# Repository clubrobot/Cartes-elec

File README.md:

View this project on [CADLAB.io](https://cadlab.io/project/28321). 

# Cartes-elec
Repo de toutes les cartes électroniques utilisées par le CRINSA. Commencé en 2025 sous Kicad 8.0

TODO:
 - Finir le pcb principal
 - Finir le pcb règle
 - Faire le PCB du lidar
 - Faire le PCB du controlleur des afficheurs Leds-Matrix (ou en tout cas le reprogrammer)
 - Faire les 3 PCBs des Superstars

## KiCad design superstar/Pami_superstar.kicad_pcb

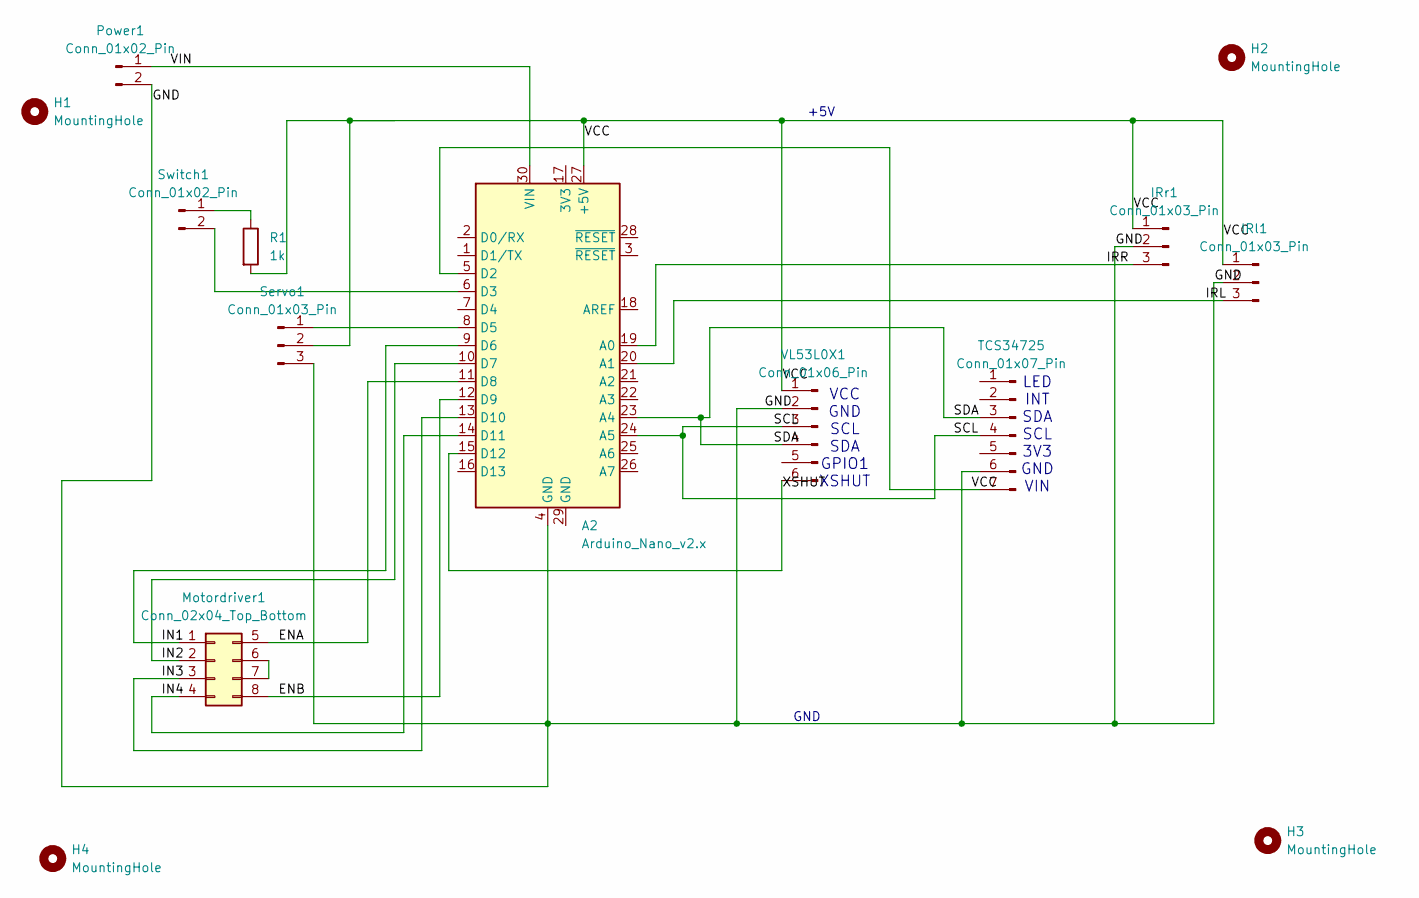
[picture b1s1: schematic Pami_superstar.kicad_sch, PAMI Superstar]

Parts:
A2: Arduino_Nano_v2.x; Arduino_Nano
H1, H2, H3, H4: MountingHole; MountingHole_3.2mm_M3
IRl1: Conn_01x03_Pin; JST_EH_B3B-EH-A_1x03_P2.50mm_Vertical
IRr1: Conn_01x03_Pin; JST_EH_B3B-EH-A_1x03_P2.50mm_Vertical
Motordriver1: Conn_02x04_Top_Bottom; JST_JWPF_B08B-JWPF-SK-R_2x04_P2.00mm_Vertical
Power1: Conn_01x02_Pin; JST_EH_B2B-EH-A_1x02_P2.50mm_Vertical
R1: 1k; R_Axial_DIN0204_L3.6mm_D1.6mm_P7.62mm_Horizontal
Servo1: Conn_01x03_Pin; JST_EH_B3B-EH-A_1x03_P2.50mm_Vertical
Switch1: Conn_01x02_Pin; JST_EH_B2B-EH-A_1x02_P2.50mm_Vertical
TCS34725: Conn_01x07_Pin; JST_EH_B7B-EH-A_1x07_P2.50mm_Vertical
VL53L0X1: Conn_01x06_Pin; JST_EH_B6B-EH-A_1x06_P2.50mm_Vertical

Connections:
/ENA: A2.11 (D8), Motordriver1.5
/ENB: A2.12 (D9), Motordriver1.8
/GND: A2.4 (GND), IRl1.2, IRr1.2, Power1.2, Servo1.3, TCS34725.6, VL53L0X1.2
/IN1: A2.9 (D6), Motordriver1.1
/IN2: A2.10 (D7), Motordriver1.2
/IN3: A2.13 (D10), Motordriver1.3
/IN4: A2.14 (D11), Motordriver1.4
/IRL: A2.20 (A1), IRl1.3
/IRR: A2.19 (A0), IRr1.3
/SCL: A2.24 (A5), TCS34725.4, VL53L0X1.3
/SDA: A2.23 (A4), TCS34725.3, VL53L0X1.4
/VCC: A2.5 (D2), A2.27 (+5V), IRl1.1, IRr1.1, R1.2, Servo1.2, TCS34725.7, VL53L0X1.1
/VIN: A2.30 (VIN), Power1.1
/XSHUT: A2.15 (D12), VL53L0X1.6
unnamed: A2.6 (D3), Switch1.2
unnamed: A2.8 (D5), Servo1.1
unnamed: Motordriver1.6, Motordriver1.7
unnamed: R1.1, Switch1.1

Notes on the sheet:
LED INT SDA SCL 3V3 GND VIN
VCC GND SCL SDA GPIO1 XSHUT
GND
+5V

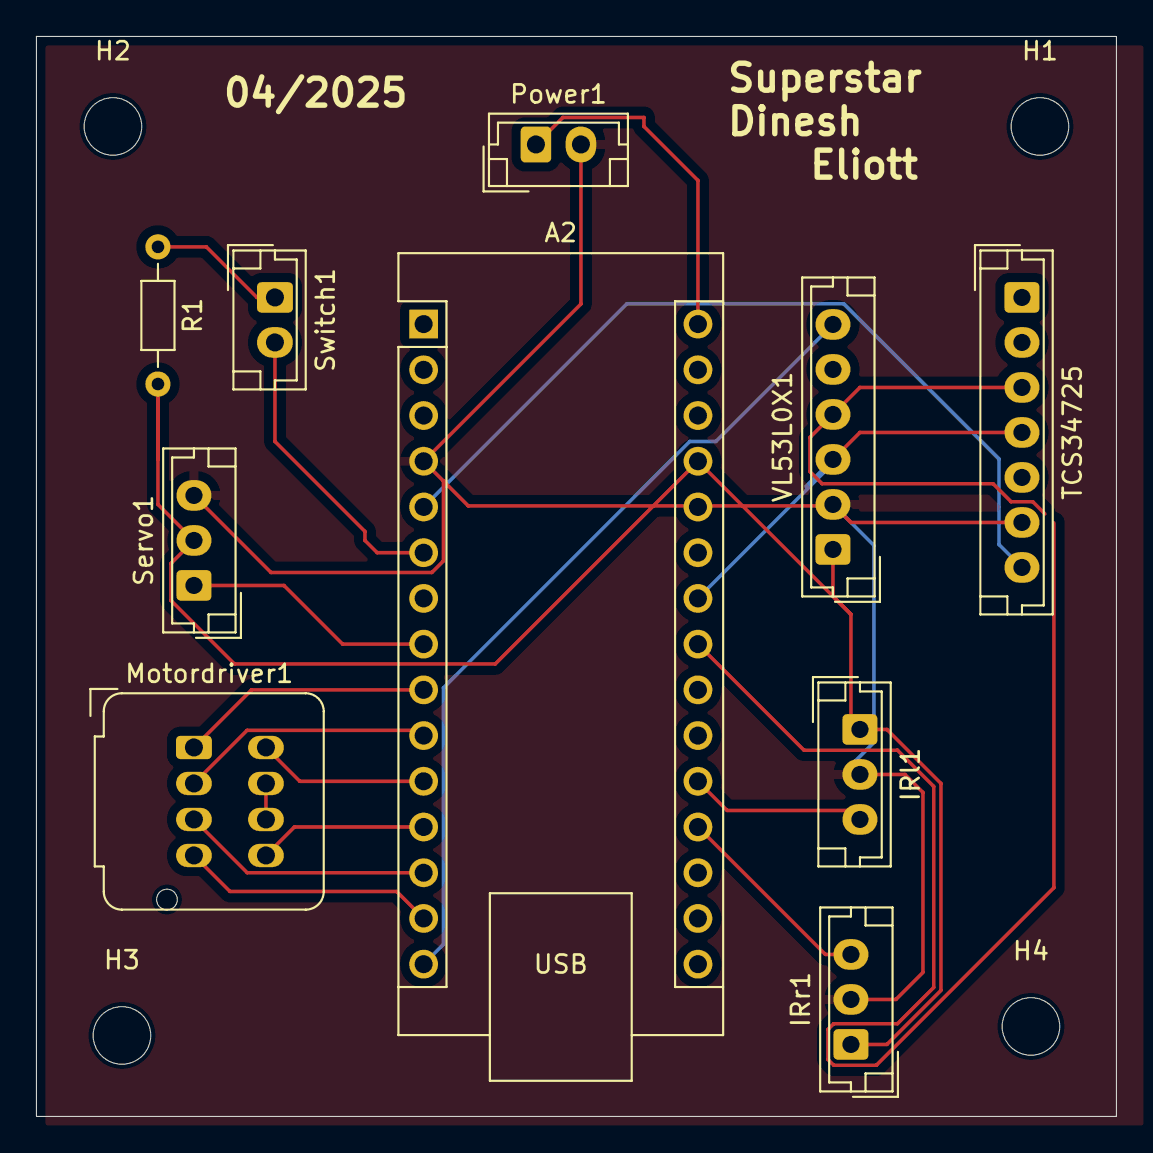
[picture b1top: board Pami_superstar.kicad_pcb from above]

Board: 2 copper layers, 60.0 x 60.0 mm, 14 parts (0 on the bottom side), 18 nets.

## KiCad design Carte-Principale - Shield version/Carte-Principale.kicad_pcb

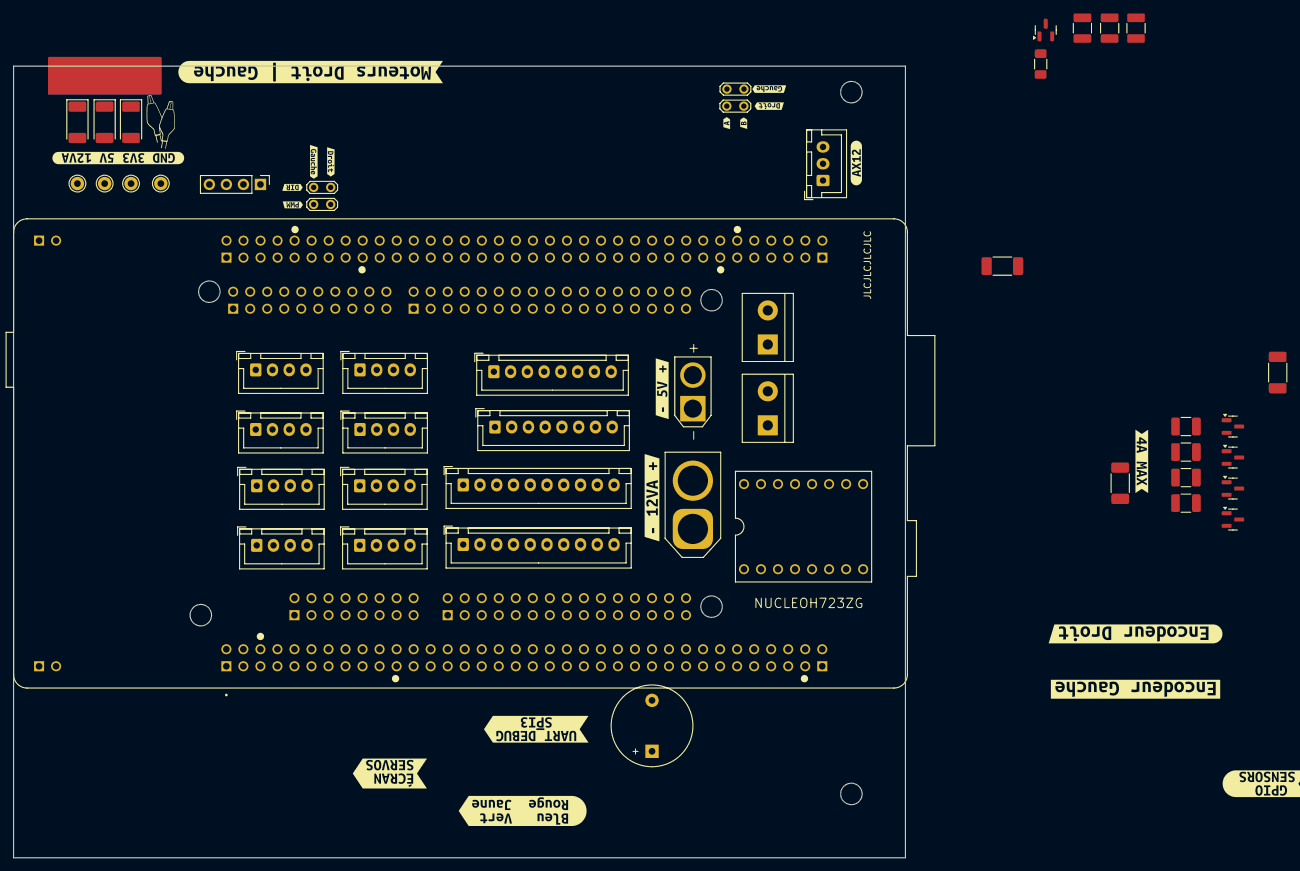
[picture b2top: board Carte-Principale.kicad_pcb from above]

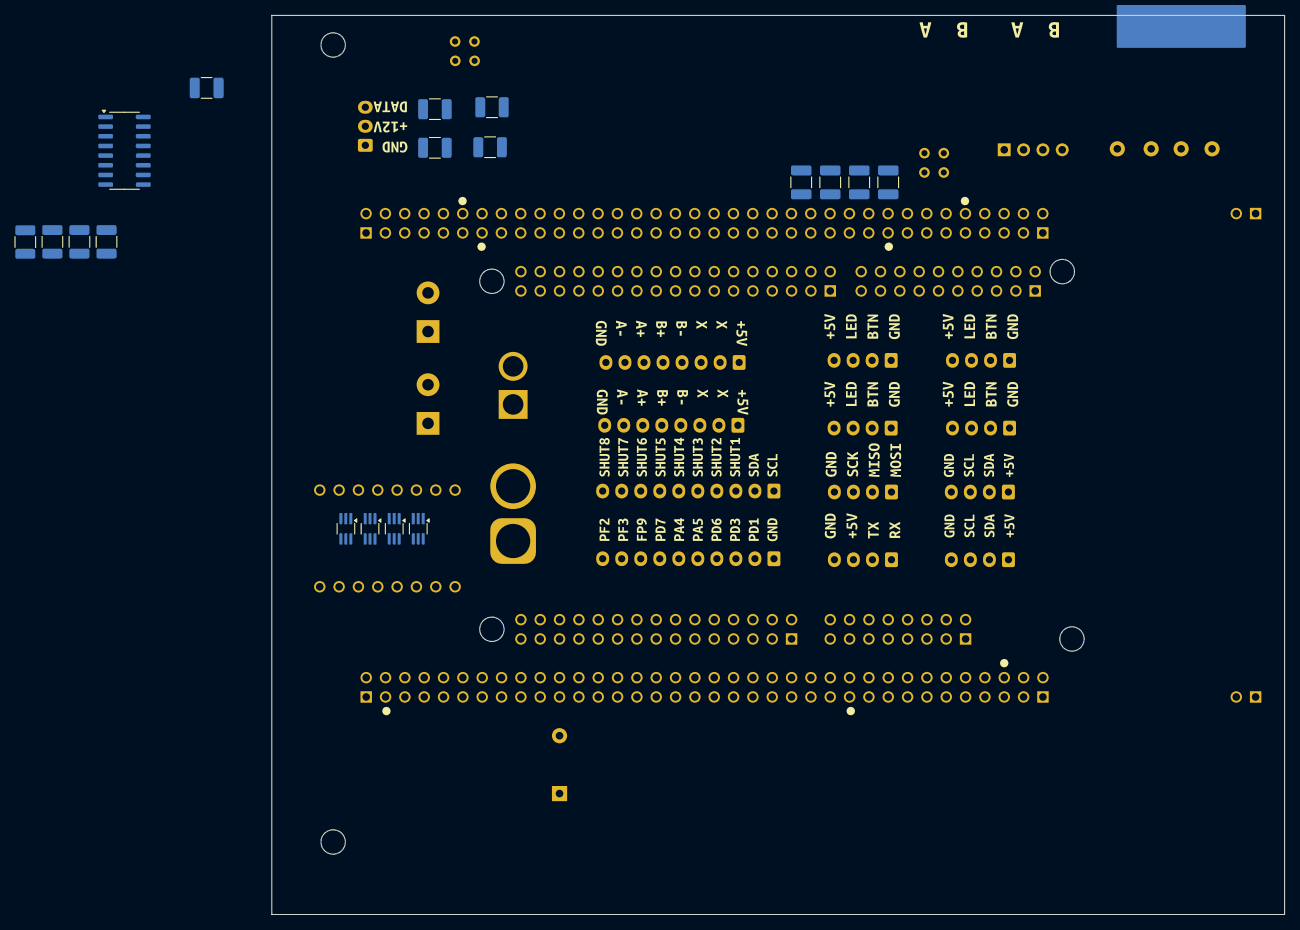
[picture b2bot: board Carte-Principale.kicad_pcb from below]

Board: 2 copper layers, 133.1 x 118.1 mm, 107 parts (34 on the bottom side), 80 nets, no tracks yet.

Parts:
BZ1: Buzzer; Buzzer_12x9.5RM7.6
C3, C4, C5, C6: 100n; C_1210_3225Metric_Pad1.33x2.70mm_HandSolder
C7: 0.1µ; C_1210_3225Metric_Pad1.33x2.70mm_HandSolder
D5: 5V; LED_2010_5025Metric_Pad1.52x2.65mm_HandSolder
D6: 3V3; LED_2010_5025Metric_Pad1.52x2.65mm_HandSolder
D7: 12VA; LED_2010_5025Metric_Pad1.52x2.65mm_HandSolder
DRV1: DRV8844_BREAKOUT_BOARD
F1, F2: 5A; Fuse_2010_5025Metric_Pad1.52x2.65mm_HandSolder
F3: 1.3A; Fuse_2010_5025Metric_Pad1.52x2.65mm_HandSolder
G1: LOGO
H1, H2, H3, H4: MountingHole; MountingHole_3.2mm_M3
J1: Moteur_Gauche; TerminalBlock_bornier-2_P5.08mm
J2: GND; PinHeader_1x04_P2.54mm_Vertical
J3: 12VA; AMASS_XT60-M_1x02_P7.20mm_Vertical
J4: 5V; AMASS_XT30U-M_1x02_P5.0mm_Vertical
J5: Moteur_Droit; TerminalBlock_bornier-2_P5.08mm
J6: UART_Debug; JST_XH_B4B-XH-A_1x04_P2.50mm_Vertical
J7: GPIO; JST_XH_B10B-XH-A_1x10_P2.50mm_Vertical
J8: Encodeur_D; JST_XH_B8B-XH-A_1x08_P2.50mm_Vertical
J9: SPI3; JST_XH_B4B-XH-A_1x04_P2.50mm_Vertical
J10: Sensors; JST_XH_B10B-XH-A_1x10_P2.50mm_Vertical
J13: Encodeur_G; JST_XH_B8B-XH-A_1x08_P2.50mm_Vertical
J15: AX12; JST_XH_B3B-XH-A_1x03_P2.50mm_Vertical
J18: PCA9685; JST_XH_B4B-XH-A_1x04_P2.50mm_Vertical
J21: I2C Screen; JST_XH_B4B-XH-A_1x04_P2.50mm_Vertical
Q1: BC817; SOT-23
Q2, Q3, Q4, Q5: BSS138; SOT-23
R1, R3, R4: R; R_1210_3225Metric_Pad1.30x2.65mm_HandSolder
R2: R; R_1206_3216Metric_Pad1.30x1.75mm_HandSolder
R9, R10, R11, R12: 10k; R_1210_3225Metric_Pad1.30x2.65mm_HandSolder
R27, R28, R29, R30: 100; R_1210_3225Metric_Pad1.30x2.65mm_HandSolder
R31, R32, R33, R34: 10K; R_1210_3225Metric_Pad1.30x2.65mm_HandSolder
SW1: Rouge; JST_XH_B4B-XH-A_1x04_P2.50mm_Vertical
SW2: Bleu; JST_XH_B4B-XH-A_1x04_P2.50mm_Vertical
SW3: Jaune; JST_XH_B4B-XH-A_1x04_P2.50mm_Vertical
SW4: Vert; JST_XH_B4B-XH-A_1x04_P2.50mm_Vertical
TP1: 3V3; Pin_D1.0mm_L10.0mm
TP2: GND; Pin_D1.0mm_L10.0mm
TP3: 5V; Pin_D1.0mm_L10.0mm
TP5: 12VA; Pin_D1.0mm_L10.0mm
TP6: Test_PWM; TestPoint_2Pads_Pitch2.54mm_Drill0.8mm
TP7: Test_DIR; TestPoint_2Pads_Pitch2.54mm_Drill0.8mm
TP8: Test_Gauche; TestPoint_2Pads_Pitch2.54mm_Drill0.8mm
TP9: Test_Droit; TestPoint_2Pads_Pitch2.54mm_Drill0.8mm
U2: NUCLEOH723ZG; MODULE_NUCLEOH723ZG
U3: AM26LV32xD; SOIC-16_3.9x9.9mm_P1.27mm
U4, U5, U6, U7: 74LVC1G3157; SOT-363_SC-70-6_Handsoldering
kibuzzard-2: G***; kibuzzard-66C478F6
kibuzzard-3: G***; kibuzzard-66C08D4F
kibuzzard-4: G***; kibuzzard-66C08D66
kibuzzard-5: G***; kibuzzard-66C08EFC
kibuzzard-7, kibuzzard-23: G***; kibuzzard-66C09269
kibuzzard-8, kibuzzard-19: G***; kibuzzard-66C0927B
kibuzzard-10: G***; kibuzzard-66C092E0
kibuzzard-22: G***; kibuzzard-66C09293
kibuzzard-24: G***; kibuzzard-66C0929D
kibuzzard-27: G***; kibuzzard-66C0922C
kibuzzard-28, kibuzzard-29: G***; kibuzzard-66C091DE
kibuzzard-30: G***; kibuzzard-66C09044
kibuzzard-34, kibuzzard-37: G***; kibuzzard-66C090AC
kibuzzard-35: G***; kibuzzard-66C09018
kibuzzard-38, kibuzzard-39, kibuzzard-40, kibuzzard-41: G***; kibuzzard-66C08FE4
kibuzzard-66F08110: G***; kibuzzard-66F08110
kibuzzard-66F08121: G***; kibuzzard-66F08121
kibuzzard-66FDA353: G***; kibuzzard-66FDA353
kibuzzard-67548A22: G***; kibuzzard-67548A22
kibuzzard-67548BCB: G***; kibuzzard-67548BCB
kibuzzard-675489B9: G***; kibuzzard-675489B9
kibuzzard-675489F8: G***; kibuzzard-675489F8
kibuzzard-675739BC: G***; kibuzzard-675739BC
kibuzzard-6754898D: G***; kibuzzard-6754898D
kibuzzard-6757392E: G***; kibuzzard-6757392E
kibuzzard-67547681: G***; kibuzzard-67547681
kibuzzard-67548783: G***; kibuzzard-67548783
kibuzzard-67548923: G***; kibuzzard-67548923
kibuzzard-67573990: G***; kibuzzard-67573990

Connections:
+3.3V: C3.2, C4.2, C5.2, C6.2, C7.1, F3.2, R1.1, TP1.1, U3.4 (G), U3.16 (VDD), U4.5 (VCC), U5.5 (VCC), U6.5 (VCC), U7.5 (VCC)
+5V: BZ1.1 (+), DRV1.SLP, F2.2, J6.3, J8.1, J13.1, J18.1, J21.1, R3.1, R31.2, R32.2, R33.2, R34.2, SW1.4 (A), SW2.4 (A), SW3.4 (A), SW4.4 (A), TP3.1, U2.CN11_6 (5V_EXT)
+12VA: DRV1.VMOT, F1.2, J15.2, R4.1, TP5.1
/AX12_RX: J15.3, U2.CN7_1 (D16/I2S_A_MCK), U2.CN7_11 (D21/I2S_B_MCK)
/DEBUG_RX: J6.1, U2.CN11_69 (PD9)
/DEBUG_TX: J6.2, U2.CN12_10 (PD8)
/Encodeur_Droit_A: TP9.1, U2.CN10_11 (A8/ADC_C_IN), U3.3 (1Y)
/Encodeur_Droit_B: TP9.2, U2.CN9_26 (D62/SAI_B_MCLK), U3.5 (2Y)
/Encodeur_Gauche_A: TP8.1, U2.CN12_62 (PF11), U3.11 (3Y)
/Encodeur_Gauche_B: TP8.2, U2.CN12_59 (PF12), U3.13 (4Y)
/Encodeurs/A+_DROITE: J8.6, R27.2, U3.2 (1A)
/Encodeurs/A+_GAUCHE: J13.6, R28.2, U3.10 (3A)
/Encodeurs/A-_DROITE: J8.7, R27.1, U3.1 (1B)
/Encodeurs/A-_GAUCHE: J13.7, R28.1, U3.9 (3B)
/Encodeurs/B+_DROITE: J8.5, R29.2, U3.6 (2A)
/Encodeurs/B+_GAUCHE: J13.5, R30.2, U3.14 (4A)
/Encodeurs/B-_DROITE: J8.4, R29.1, U3.7 (2B)
/Encodeurs/B-_GAUCHE: J13.4, R30.1, U3.15 (4B)
/I2C1_SCL: J18.3, J21.3, U2.CN12_17 (PB6)
/I2C1_SDA: J18.2, J21.2, U2.CN11_21 (PB7)
/I2C2_SCL: J10.1, U2.CN9_19 (D69/I2C_B_SCL)
/I2C2_SDA: J10.2, U2.CN9_21 (D68/I2C_B_SDA)
/Moteurs/IN1: DRV1.IN1, U6.4
/Moteurs/IN2: DRV1.IN2, U7.4
/Moteurs/IN3: DRV1.IN3, U5.4
/Moteurs/IN4: DRV1.IN4, U4.4
/Moteurs/MOTOR1A: DRV1.1A, J1.1
/Moteurs/MOTOR1B: DRV1.1B, J1.2
/Moteurs/MOTOR2A: DRV1.2A, J5.1
/Moteurs/MOTOR2B: DRV1.2B, J5.2
/PA4: J7.6, U2.CN7_17 (D24/SPI_B_NSS)
/PA5: J7.5, U2.CN7_10 (D13/SPI_A_SCK)
/PA6: R2.1, U2.CN7_12 (D12/SPI_A_MISO)
/PA15: DRV1.RST, U2.CN7_9 (D20/I2S_B_WS)
/PB2: J9.1, U2.CN9_13 (D72/COMP1_INP)
/PB12: DRV1.FLT, U2.CN7_7 (D19/I2S_A_WS)
/PB13: DRV1.EN1, U2.CN7_5 (D18/I2S_A_CK)
/PB15: DRV1.EN2, U2.CN7_3 (D17/I2S_A_SD)
/PC8: R32.1, SW3.2, U2.CN8_2 (D43/SDMMC_D0)
/PC9: Q5.1 (G), R12.2, U2.CN8_4 (D44/SDMMC_D1/I2S_A_CKIN)
/PC10: J9.3, U2.CN8_6 (D45/SDMMC_D2)
/PC11: J9.2, U2.CN8_8 (D46/SDMMC_D3)
/PC12: R31.1, SW2.2, U2.CN8_10 (D47/SDMMC_CK)
/PD1: J10.3, U2.CN9_27 (D66/CAN_TX)
/PD2: R33.1, SW4.2, U2.CN8_12 (D48/SDMMC_CMD)
/PD3: J10.10, U2.CN9_10 (D55/USART_B_CTS)
/PD4: R34.1, SW1.2, U2.CN9_8 (D54/USART_B_RTS)
/PD5: Q2.1 (G), R11.2, U2.CN9_6 (D53/USART_B_TX)
/PD6: J7.4, U2.CN9_4 (D52/USART_B_RX)
/PD7: J7.7, U2.CN9_2 (D51/USART_B_SCLK)
/PE0: J7.2, U2.CN10_33 (D34/TIMER_B_ETR)
/PE2: J10.4, U2.CN9_14 (D56/SAI_A_MCLK)
/PE3: J10.5, U2.CN9_22 (D60/SAI_B_SD)
/PE4: J10.6, U2.CN9_16 (D57/SAI_A_FS)
/PE5: J10.7, U2.CN9_18 (D58/SAI_A_SCK)
/PE9: TP6.1, U2.CN10_4 (D6/TIMER_A_PWM1), U4.1, U5.3
/PE11: TP6.2, U2.CN10_6 (D5/TIMER_A_PWM2), U6.3, U7.1
/PF2: J7.10, U2.CN9_17 (D70/I2C_B_SMBA)
/PF3: J7.9, U2.CN7_20 (D8/IO)
/PF4: TP7.2, U2.CN10_7 (A6/ADC_A_IN), U6.6, U7.6
/PF5: TP7.1, U2.CN10_9 (A7/ADC_B_IN), U4.6, U5.6
/PF8: J7.3, U2.CN9_24 (D61/SAI_B_SCK)
/PF9: J7.8, U2.CN9_28 (D63/SAI_B_FS)
/PG0: J10.8, U2.CN9_29 (D65/IO)
/PG1: J10.9, U2.CN9_30 (D64/IO)
/PG2: Q3.1 (G), R10.2, U2.CN8_14 (D49/IO)
/PG3: Q4.1 (G), R9.2, U2.CN8_16 (D50/IO)
GND: C3.1, C4.1, C5.1, C6.1, C7.2, D5.1 (K), D6.1 (K), D7.1 (K), DRV1.GND, DRV1.GND1, J2.1, J2.2, J2.3, J2.4, J3.1, J4.1, J6.4, J7.1, J8.8, J9.4, J13.8, J15.1, J18.4, J21.4, Q1.2 (E), Q2.2 (S), Q3.2 (S), Q4.2 (S), Q5.2 (S), R9.1, R10.1, R11.1, R12.1, SW1.1, SW2.1, SW3.1, SW4.1, TP2.1, U2.CN3_1 (GND_CN3), U2.CN3_2 (GND_CN3), U2.CN4_1 (GND_CN4), U2.CN4_2 (GND_CN4), U2.CN7_8 (GND_CN7), U2.CN8_11 (GND_CN8), U2.CN8_13 (GND_CN8), U2.CN9_12 (GND_CN9), U2.CN9_23 (GND_CN9), U2.CN10_3 (AGND_CN10), U2.CN10_5 (GND_CN10), U2.CN10_17 (GND_CN10), U2.CN10_22 (GND_CN10), U2.CN10_27 (GND_CN10), U2.CN11_8 (GND_CN11), U2.CN11_19 (GND_CN11), U2.CN11_20 (GND_CN11), U2.CN11_22 (GND_CN11), U2.CN11_49 (GND_CN11), U2.CN11_60 (GND_CN11), U2.CN12_9 (GND_CN12), U2.CN12_20 (GND_CN12), U2.CN12_32 (AGND_CN12), U2.CN12_39 (GND_CN12), U2.CN12_54 (GND_CN12), U2.CN12_63 (GND_CN12), U2.CN15_1 (GND_CN15), U2.CN15_2 (GND_CN15), U2.CN16_1 (GND_CN16), U2.CN16_2 (GND_CN16), U3.8 (GND), U3.12 (~G), U4.2 (GND), U4.3, U5.1, U5.2 (GND), U6.1, U6.2 (GND), U7.2 (GND), U7.3
unnamed: BZ1.2 (-), Q1.3 (C)
unnamed: D5.2 (A), R3.2
unnamed: D6.2 (A), R1.2
unnamed: D7.2 (A), R4.2
unnamed: F1.1, J3.2
unnamed: F2.1, J4.2
unnamed: Q1.1 (B), R2.2
unnamed: Q2.3 (D), SW4.3 (K)
unnamed: Q3.3 (D), SW3.3 (K)
unnamed: Q4.3 (D), SW2.3 (K)
unnamed: Q5.3 (D), SW1.3 (K)
unnamed: F3.1, U2.CN8_7 (3V3_CN8)

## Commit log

2024-07-29 Backlink to CADLAB.io has been added.
2024-07-29 Hiérarchie
2024-07-29 Moteurs + Encodeurs
2024-07-30 Avancée Actionneur
2024-08-01 Rajout écran
2024-08-04 wiring
2024-08-12 Schéma vérifié
2024-08-16 Avancée PCB
2024-08-20 avancée
2024-08-23 Final pcb modification
2024-10-30 Cartes élec à refaire et TODO
2024-12-09 FInal
2025-05-05 abcdefgh
